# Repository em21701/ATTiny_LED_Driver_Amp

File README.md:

ATTiny_LED_Driver
=================

LED Driver Board using and ATTiny processor for PWM and effects.

The goal of this project is to use the ATTiny as a Buck Driver for High Brightness LEDs. 
After getting a functional Buck Driver working I will add blink effects.

This driver board has 2 inputs and is intended for use as a turn signal/running light 
combo and brake light/running light combo for a motorcycle. As such the board has 2 inputs,
one for 12v power from the key and a second for 12v power from either the turn signal or 
brake light. The Key inuput will illuminate the LEDs to a low level and the second input 
will change the brightness to a significantly higher level.Blink effects will be added when 
used as a tail/brake combo to make the light more conspicuous. 

Currently planned blink effects are an invverted heartbeat and flash and fade. In the heart 
beat pattern the light will dim in a lub-dub pattern while brake light is illuminated. 
In the flash and fade pattern, the brake light will flash to full brightness then slowly fade
to a level brighter than running light level, but noticeably lower than full brightness. The
light will then flash back to full brightness and repeat.

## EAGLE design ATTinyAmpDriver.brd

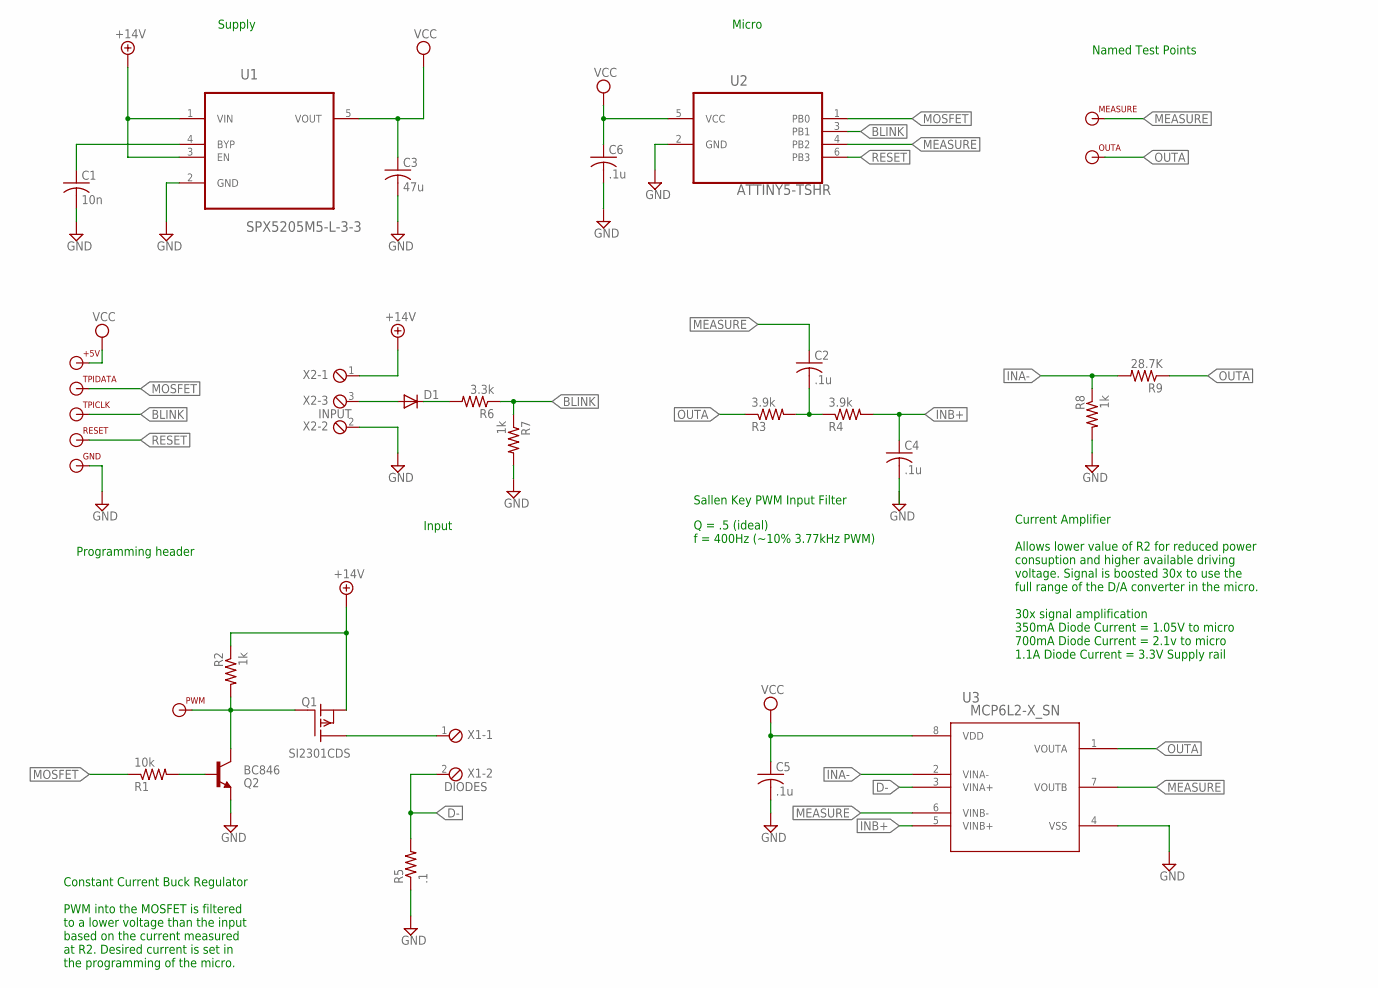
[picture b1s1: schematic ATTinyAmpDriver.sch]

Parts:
+5V: TPI; TPI_PAD
C1: 10n; C0603; DIGIKEY 445-1311-1-ND
C2, C4, C5, C6: .1u; C0603; DIGIKEY 445-1316-1-ND
C3: 47u; C1206; DIGIKEY 399-5508-1-ND
D1: DIODE_0603; D0603; DIGIKEY 641-1002-1-ND
GND: TPI; TPI_PAD
MEASURE: TPI; TPI_PAD
OUTA: TPI; TPI_PAD
PWM: TPI; TPI_PAD
Q1: SI2301CDS; SOT-23_POWER; DIGIKEY 568-6956-1-ND
Q2: BC846; SOT23; DIGIKEY BC846BMTFCT-ND
R1: 10k; R0603; DIGIKEY RMCF0603FT10K0CT-ND
R2, R7, R8: 1k; R0603; DIGIKEY RMCF0603FT1K00CT-ND
R3, R4: 3.9k; R0603; DIGIKEY RMCF0603FT3K90CT-ND
R5: .1; R1206; DIGIKEY A103268CT-ND
R6: 3.3k; R0603; DIGIKEY RMCF0603FT3K30CT-ND
R9: 28.7K; R0603; DIGIKEY RMCF0603FT28R7CT-ND
RESET: TPI; TPI_PAD
TPICLK: TPI; TPI_PAD
TPIDATA: TPI; TPI_PAD
U1: SPX5205M5-L-3-3; SOT95P280X145-5N; DIGIKEY 1016-1251-ND
U2: ATTINY5-TSHR; SOT95P280X145-6N; DIGIKEY ATTINY10-TSHRCT-ND
U3: MCP6L2-X_SN; SOIC8-N_MC; DIGIKEY MCP6L2T-E/SNCT-ND
X1: DIODES; 2POL254
X2: INPUT; 3POL254

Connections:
+14V: Q1.P$2 (S), R2.1, U1.1 (VIN), U1.3 (EN), X2.1
BLINK: R6.1, R7.1, TPICLK.P$1, U2.3 (PB1)
D-: R5.2, U3.3 (VINA+), X1.2
GND: C1.2, C3.2, C4.2, C5.2, C6.2, GND.P$1, Q2.2 (E), R5.1, R7.2, R8.2, U1.2 (GND), U2.2 (GND), U3.4 (VSS), X2.2
INA-: R8.1, R9.2, U3.2 (VINA-)
INB+: C4.1, R4.2, U3.5 (VINB+)
MEASURE: C2.1, MEASURE.P$1, U2.4 (PB2), U3.6 (VINB-), U3.7 (VOUTB)
MOSFET: R1.1, TPIDATA.P$1, U2.1 (PB0)
unnamed: D1.1A (A), X2.3
unnamed: C1.1, U1.4 (BYP)
unnamed: Q1.P$3 (D), X1.1
unnamed: D1.2C (C), R6.2
unnamed: PWM.P$1, Q1.P$1 (G), Q2.3 (C), R2.2
unnamed: Q2.1 (B), R1.2
unnamed: C2.2, R3.2, R4.1
OUTA: OUTA.P$1, R3.1, R9.1, U3.1 (VOUTA)
RESET: RESET.P$1, U2.6 (PB3)
VCC: +5V.P$1, C3.1, C5.1, C6.1, U1.5 (VOUT), U2.5 (VCC), U3.8 (VDD)

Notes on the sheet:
Supply
Micro
Input
Programming header
Current Amplifier Allows lower value of R2 for reduced power consuption and higher available driving voltage. Signal is boosted 30x to use the full range of the D/A converter in the micro. 30x signal amplification 350mA Diode Current = 1.05V to micro 700mA Diode Current = 2.1v to micro 1.1A Diode C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
Constant Current Buck Regulator PWM into the MOSFET is filtered to a lower voltage than the input based on the current measured at R2. Desired current is set in the programming of the micro.
Sallen Key PWM Input Filter
Q = .5 (ideal) f = 400Hz (~10% 3.77kHz PWM)
Named Test Points

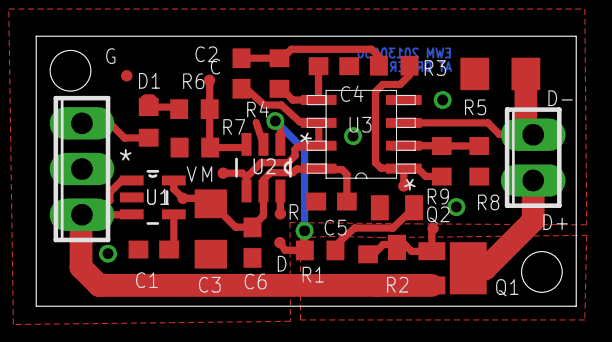
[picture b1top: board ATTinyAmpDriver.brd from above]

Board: 2 copper layers, 30.0 x 15.0 mm, 31 parts (0 on the bottom side), 18 nets.

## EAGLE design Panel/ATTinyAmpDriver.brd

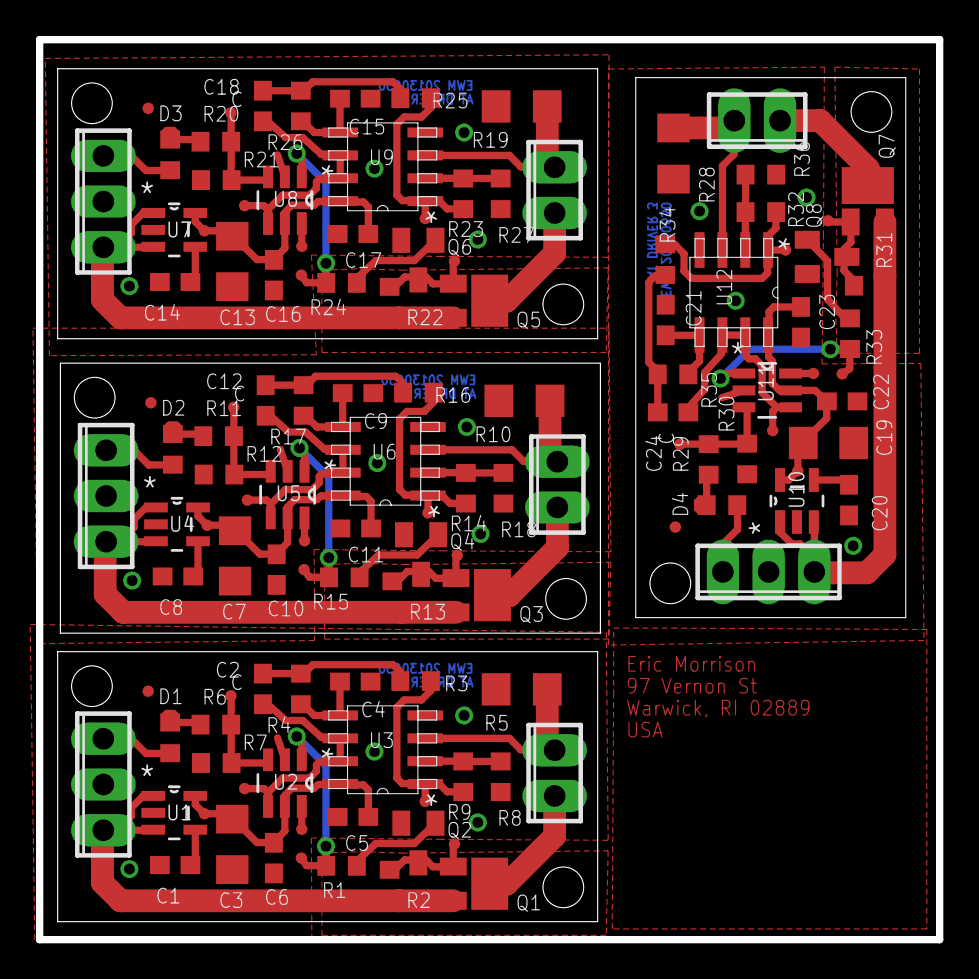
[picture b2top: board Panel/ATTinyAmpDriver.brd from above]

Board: 2 copper layers, 50.0 x 50.0 mm, 125 parts (0 on the bottom side), 72 nets.

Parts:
+5V, +5V1, +5V2, +5V3: TPI; TPI_PAD
C1, C8, C14, C20: 10n; C0603
C2, C4, C5, C6, C9, C10, C11, C12, C15, C16, C17, C18, C21, C22, C23, C24: .1u; C0603
C3, C7, C13, C19: 47u; C1206
D1, D2, D3, D4: DIODE_0603; D0603
DRILEGEND: DRILEGEND
GND, GND1, GND2, GND3: TPI; TPI_PAD
MEASURE, MEASURE1, MEASURE2, MEASURE3: TPI; TPI_PAD
OUTA, OUTA1, OUTA2, OUTA3: TPI; TPI_PAD
PWM, PWM1, PWM2, PWM3: TPI; TPI_PAD
Q1, Q3, Q5, Q7: SI2301CDS; SOT-23_POWER
Q2, Q4, Q6, Q8: BC846; SOT23
R1, R15, R24, R33: 10k; R0603
R2, R7, R8, R12, R13, R18, R21, R22, R27, R30, R31, R36: 1k; R0603
R3, R4, R16, R17, R25, R26, R34, R35: 3.9k; R0603
R5, R10, R19, R28: .1; R1206
R6, R11, R20, R29: 3.3k; R0603
R9, R14, R23, R32: 28.7K; R0603
RESET, RESET1, RESET2, RESET3: TPI; TPI_PAD
TPICLK, TPICLK1, TPICLK2, TPICLK3: TPI; TPI_PAD
TPIDATA, TPIDATA1, TPIDATA2, TPIDATA3: TPI; TPI_PAD
U1, U4, U7, U10: SPX5205M5-L-3-3; SOT95P280X145-5N
U2, U5, U8, U11: ATTINY5-TSHR; SOT95P280X145-6N
U3, U6, U9, U12: MCP6L2-X_SN; SOIC8-N_MC
X1, X4, X6, X8: DIODES; 2POL254
X2, X3, X5, X7: INPUT; 3POL254

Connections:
+14V: Q1.P$2, R2.1, U1.1, U1.3, X2.1
+14V1: Q3.P$2, R13.1, U4.1, U4.3, X3.1
+14V2: Q5.P$2, R22.1, U7.1, U7.3, X5.1
+14V3: Q7.P$2, R31.1, U10.1, U10.3, X7.1
BLINK: R6.1, R7.1, TPICLK.P$1, U2.3
BLINK1: R11.1, R12.1, TPICLK1.P$1, U5.3
BLINK2: R20.1, R21.1, TPICLK2.P$1, U8.3
BLINK3: R29.1, R30.1, TPICLK3.P$1, U11.3
D-: R5.2, U3.3, X1.2
D-1: R10.2, U6.3, X4.2
D-2: R19.2, U9.3, X6.2
D-3: R28.2, U12.3, X8.2
GND: C1.2, C3.2, C4.2, C5.2, C6.2, GND.P$1, Q2.2, R5.1, R7.2, R8.2, U1.2, U2.2, U3.4, X2.2
GND1: C7.2, C8.2, C9.2, C10.2, C11.2, GND1.P$1, Q4.2, R10.1, R12.2, R18.2, U4.2, U5.2, U6.4, X3.2
GND2: C13.2, C14.2, C15.2, C16.2, C17.2, GND2.P$1, Q6.2, R19.1, R21.2, R27.2, U7.2, U8.2, U9.4, X5.2
GND3: C19.2, C20.2, C21.2, C22.2, C23.2, GND3.P$1, Q8.2, R28.1, R30.2, R36.2, U10.2, U11.2, U12.4, X7.2
INA-: R8.1, R9.2, U3.2
INA-1: R14.2, R18.1, U6.2
INA-2: R23.2, R27.1, U9.2
INA-3: R32.2, R36.1, U12.2
INB+: C4.1, R4.2, U3.5
INB+1: C9.1, R17.2, U6.5
INB+2: C15.1, R26.2, U9.5
INB+3: C21.1, R35.2, U12.5
MEASURE: C2.1, MEASURE.P$1, U2.4, U3.6, U3.7
MEASURE1: C12.1, MEASURE1.P$1, U5.4, U6.6, U6.7
MEASURE2: C18.1, MEASURE2.P$1, U8.4, U9.6, U9.7
MEASURE3: C24.1, MEASURE3.P$1, U11.4, U12.6, U12.7
MOSFET: R1.1, TPIDATA.P$1, U2.1
MOSFET1: R15.1, TPIDATA1.P$1, U5.1
MOSFET2: R24.1, TPIDATA2.P$1, U8.1
MOSFET3: R33.1, TPIDATA3.P$1, U11.1
unnamed: D1.1A, X2.3
unnamed: C1.1, U1.4
unnamed: Q1.P$3, X1.1
unnamed: D1.2C, R6.2
unnamed: PWM.P$1, Q1.P$1, Q2.3, R2.2
unnamed: Q2.1, R1.2
unnamed: Q3.P$3, X4.1
unnamed: C2.2, R3.2, R4.1
unnamed: C8.1, U4.4
unnamed: PWM1.P$1, Q3.P$1, Q4.3, R13.2
unnamed: Q4.1, R15.2
unnamed: C12.2, R16.2, R17.1
unnamed: D2.1A, X3.3
unnamed: D2.2C, R11.2
unnamed: Q5.P$3, X6.1
unnamed: C14.1, U7.4
unnamed: PWM2.P$1, Q5.P$1, Q6.3, R22.2
unnamed: Q6.1, R24.2
unnamed: C18.2, R25.2, R26.1
unnamed: D3.1A, X5.3
unnamed: D3.2C, R20.2
unnamed: Q7.P$3, X8.1
unnamed: C20.1, U10.4
unnamed: PWM3.P$1, Q7.P$1, Q8.3, R31.2
unnamed: Q8.1, R33.2
unnamed: C24.2, R34.2, R35.1
unnamed: D4.1A, X7.3
unnamed: D4.2C, R29.2
OUTA: OUTA.P$1, R3.1, R9.1, U3.1
OUTA1: OUTA1.P$1, R14.1, R16.1, U6.1
OUTA2: OUTA2.P$1, R23.1, R25.1, U9.1
OUTA3: OUTA3.P$1, R32.1, R34.1, U12.1
RESET: RESET.P$1, U2.6
RESET1: RESET1.P$1, U5.6
RESET2: RESET2.P$1, U8.6
RESET3: RESET3.P$1, U11.6
VCC: +5V.P$1, C3.1, C5.1, C6.1, U1.5, U2.5, U3.8
VCC1: +5V1.P$1, C7.1, C10.1, C11.1, U4.5, U5.5, U6.8
VCC2: +5V2.P$1, C13.1, C16.1, C17.1, U7.5, U8.5, U9.8
VCC3: +5V3.P$1, C19.1, C22.1, C23.1, U10.5, U11.5, U12.8

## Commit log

2013-05-17 Initial Commit
    Modified the ATTiny Driver Rev2 Board to include a lower value current
    sense resistor and and amplifier to bring sensing range closer to full
    scale ADC range.
2013-05-17 Fixed Broken link between Board and Schematic.
    Fixed Broken link between Board and Schematic. Created BOM
2013-05-20 Added code samples
2013-06-11 P Channel MOSFET
    Changed from Incorrect N-Channel to P-Channel High side switch on the
    Driver Circuit.
2013-06-12 Added Driving transistor for P-FET
    Added driver transistor to P Channel MOSFET and capacitor to op-amp
    output.
2013-06-13 Added buck driver code:
2013-06-13 Removed LED filter circuit
2013-06-13 Hopefully this will get the ADC functioning
2013-06-14 ATStudio Driver ADC function test
2013-06-14 Still working on getting the ADC functioning
2013-06-16 Code is working better now
2013-06-16 Removed Cap from OpAmp Output
2013-06-17 PanicFlag changed to uint8_t
2013-06-17 Changed code to reduce wasted operations
2013-06-20 Low Pass filter before OpAmp
2013-06-21 Blink code moved to ISR for thread safety
2013-06-21 Changed PWM filter to Sallen Key
2013-06-23 Added a diode to Blink input to prevent back feed if transistor shorts
2013-06-23 Changed blink diode to regular rectifier diode
2013-06-28 Changed Schematic Layout
2013-07-01 Working code and matching board and schematic
2013-07-01 Updated BOM
2013-07-02 Added Newark pricing to some components
2013-07-03 Added test points around op-amp filter
2013-07-09 Panelized
2013-07-09 Changed C3 to 1206 47uF
2013-07-09 Cleaned up buck code, created buck patterns dir
2013-07-10 Started work on blink flash.
2013-07-10 ATStudio pattern source added.
    New OpAmp is allowing better input, lower sensitivty to the panic
    threshold is required.
2013-07-12 8MHz Clock on ATStudio code
2013-07-12 8MHz clock is working ATStudio code
2013-07-13 Working pulse and heartbeat code
2013-07-14 Unified codebase, added flash_beat pattern
2013-07-14 Changed Flash_Beat to slower initial flash rate
2013-07-15 Unified ATStudio and Eclipse code versions
2013-07-16 Panel Change
2013-07-17 Panel Update
2013-07-25 Created Programming Fixture
2013-08-01 Changed speed of level change
    Added variables to store previously working values when changing between
    light levels. During the change the PWM is set to the last working value
    for that level. This is currently untested.
2013-08-06 Updated masks and fixture
